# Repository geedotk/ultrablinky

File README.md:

# Ultrablinky Hardware

Ultrablinky is a strobelight/stroboscope that has multiple blink modes and can be triggered by different stimuli. If blinking an LED is the "Hello, world!" of the hardware/firmware world, Ultrablinky is the equivalent of shouting "HELLO, WORLD!"

## Use cases:
- Camera strobe, where a set number of flashes are triggered by motion
- Continuous flashing, because you know you want to pretend like you're at a rave
- Flashing synchronized with sound, because you still want to pretend you're at a rave, but you got tired of the asynchronous flashing
- Continuous flashing to freeze repetitive motion. Although it will look like the motion is stopped, don't be an idiot and stick your fingers in it, because it will hurt.
- Do other cool stuff that hasn't been thought of yet.

## Hardware
The "blinky" in the Ultrablinky is a 100W COB LED. This LED has forward voltage Vf of
30V-36V with a current of 3.5A.

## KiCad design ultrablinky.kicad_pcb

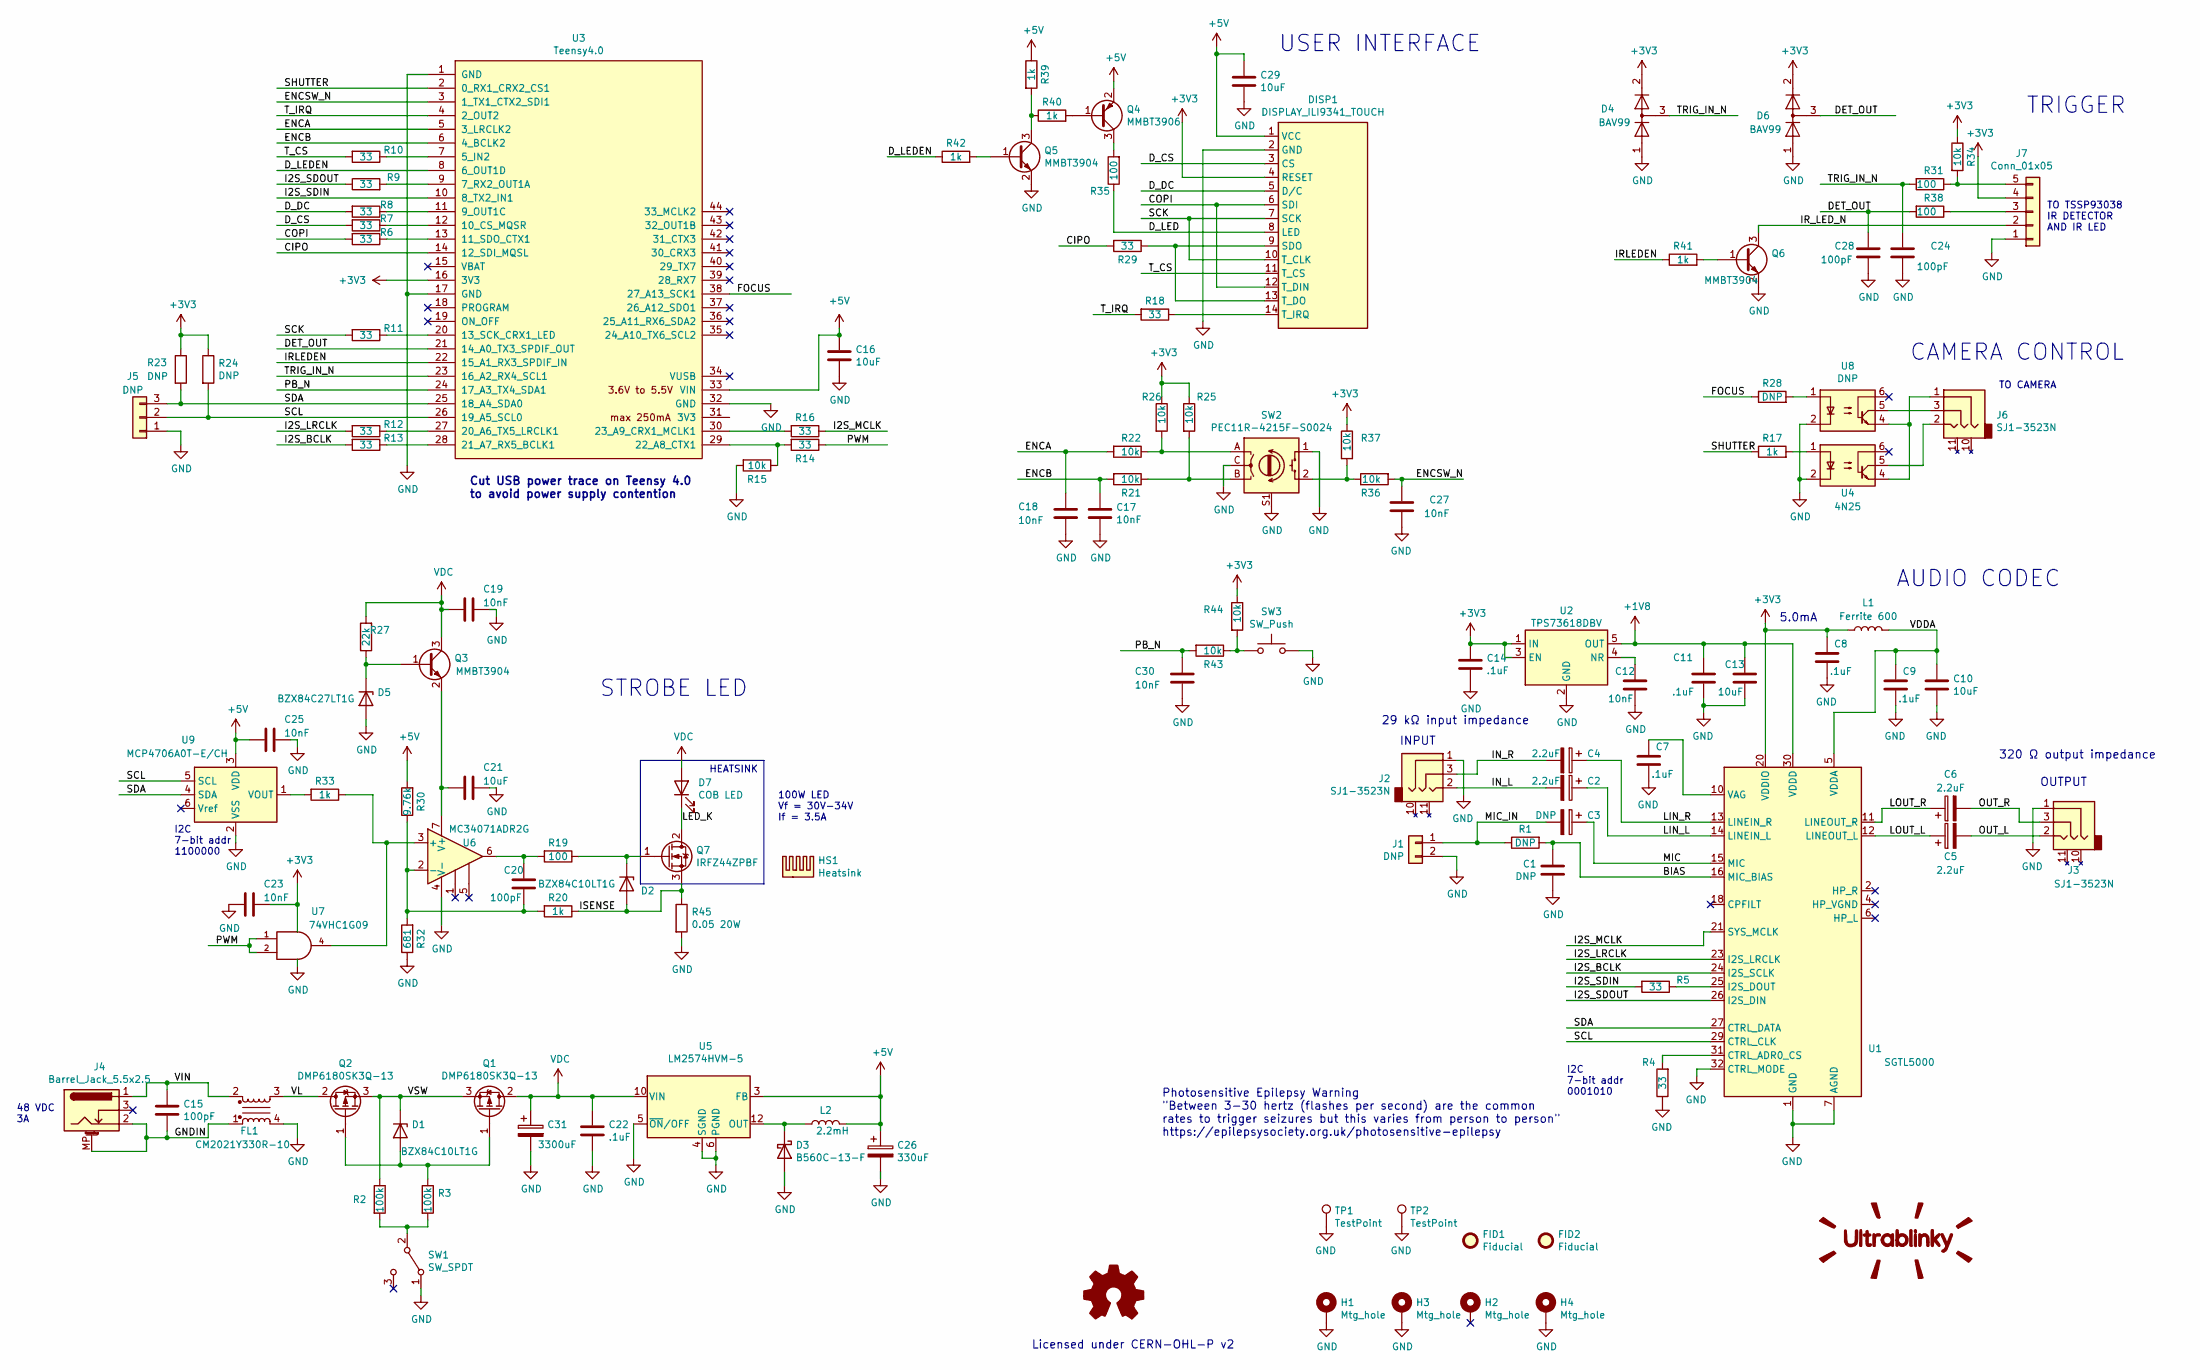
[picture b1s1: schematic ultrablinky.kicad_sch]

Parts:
C1: DNP; C_1206_3216Metric
C2, C4, C5, C6: 2.2uF; CP_Elec_4x5.7
C3: DNP; CP_Elec_4x5.7
C7, C8, C9, C11, C14, C22: .1uF; R_0805_2012Metric
C10, C13, C16, C21, C29: 10uF; C_1206_3216Metric
C12, C17, C18, C19, C23, C25, C27, C30: 10nF; C_0805_2012Metric
C15, C20, C24, C28: 100pF; C_0805_2012Metric
C26: 330uF; CP_Elec_8x10
C31: 3300uF; CP_Radial_L40.0mm_D20.0mm_P7.50mm_Horizontal
D1, D2: BZX84C10LT1G; D_SOT-23_ANK
D3: B560C-13-F; D_SMC
D4, D6: BAV99; SOT-23
D5: BZX84C27LT1G; D_SOT-23_ANK
D7: COB LED; LED_COB_100W
DISP1: DISPLAY_ILI9341_TOUCH
FID1, FID2: Fiducial; Fiducial_1mm_Mask2mm
FL1: CM2021Y330R-10; CM2021Y330R10
H1, H2, H3, H4: Mtg_hole; MountingHole_3.2mm_M3_DIN965_Pad
HS1: Heatsink; Heatsink_70x70mm_ATS-CPX070070025-136-C2-R0
J1: DNP; PinHeader_1x02_P2.54mm_Vertical
J2, J3, J6: SJ1-3523N; SJ13523N1_TRS_Jack
J4: Barrel_Jack_5.5x2.5; CUI_PJ-079BH
J5: DNP; PinHeader_1x03_P2.54mm_Vertical
J7: Conn_01x05; Molex_Mini-Fit_Jr_39-30-3055_1x05_P4.20mm_Horizontal
L1: Ferrite 600; L_0805_2012Metric
L2: 2.2mH; L_12x12mm_H10mm
LOGO1: Ultrablinky_logo; logo_ultrablinky
LOGO2: Logo_Open_Hardware_Small; OSHW-Logo2_9.8x8mm_SilkScreen
Q1, Q2: DMP6180SK3Q-13; TO-252-2
Q3, Q5, Q6: MMBT3904; SOT-23
Q4: MMBT3906; SOT-23
Q7: IRFZ44ZPBF; TO-220-3_Horizontal_TabDown
R1, R23, R24, R28: DNP; R_0805_2012Metric
R2, R3: 100k; R_0805_2012Metric
R4, R5, R6, R7, R8, R9, R10, R11, R12, R13, R14, R16, R18, R29: 33; R_0805_2012Metric
R15, R21, R22, R25, R26, R34, R36, R37, R43, R44: 10k; R_0805_2012Metric
R17, R20, R33, R39, R40, R41, R42: 1k; R_0805_2012Metric
R19, R31, R35, R38: 100; R_0805_2012Metric
R27: 22k; R_0805_2012Metric
R30: 9.76k; R_0805_2012Metric
R32: 681; R_0805_2012Metric
R45: 0.05 20W; TO-220-2_Horizontal_TabDown
SW1: SW_SPDT; SW_EG1213
SW2: PEC11R-4215F-S0024
SW3: SW_Push; SW_PUSH_6mm_H17mm
TP1, TP2: TestPoint; TestPoint_Keystone_5006
U1: SGTL5000; QFN-32-1EP_5x5mm_P0.5mm_EP3.6x3.6mm
U2: TPS73618DBV; SOT-23-5
U3: Teensy4.0; Teensy40
U4: 4N25; 4N25_OPTOCOUPLER_SMD
U5: LM2574HVM-5; SOIC-14W_7.5x9mm_P1.27mm
U6: MC34071ADR2G; SOIC-8_3.9x4.9mm_P1.27mm
U7: 74VHC1G09; SOT-353_SC-70-5_Handsoldering
U8: DNP; 4N25_OPTOCOUPLER_SMD
U9: MCP4706A0T-E/CH; SOT-23-6

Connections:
+1V8: C11.1, C13.1, U1.30 (VDDD), U2.5 (OUT)
+3V3: C8.1, C14.1, C23.1, D4.2 (A), D6.2 (A), DISP1.4 (RESET), J7.4, L1.1, R23.1, R24.1, R25.1, R26.1, R34.1, R37.1, R44.1, U1.20 (VDDIO), U2.1 (IN), U2.3 (EN), U3.16 (3V3), U7.5 (VCC)
+5V: C16.1, C25.2, C26.1, C29.1, DISP1.1 (VCC), L2.2, Q4.2 (E), R30.2, R39.1, U3.33 (VIN), U5.3 (FB), U9.3 (VDD)
/BIAS: C1.1, R1.2, U1.16 (MIC_BIAS)
/CIPO: R29.2, U3.14 (12_SDI_MQSL)
/COPI: DISP1.6 (SDI), DISP1.12 (T_DIN), R6.2
/DET_OUT: C28.1, D6.3 (K), R38.2, U3.21 (14_A0_TX3_SPDIF_OUT)
/D_CS: DISP1.3 (CS), R7.2
/D_DC: DISP1.5 (D/C), R8.2
/D_LED: DISP1.8 (LED), R35.1
/D_LEDEN: R42.1, U3.8 (6_OUT1D)
/ENCA: C18.1, R22.2, U3.5 (3_LRCLK2)
/ENCB: C17.1, R21.2, U3.6 (4_BCLK2)
/ENCSW_N: C27.1, R36.2, U3.3 (1_TX1_CTX2_SDI1)
/FOCUS: R28.1, U3.38 (27_A13_SCK1)
/GNDIN: C15.2, FL1.1, J4.2, J4.MP (MountPin)
/I2S_BCLK: R13.2, U1.24 (I2S_SCLK)
/I2S_LRCLK: R12.2, U1.23 (I2S_LRCLK)
/I2S_MCLK: R16.1, U1.21 (SYS_MCLK)
/I2S_SDIN: R5.2, U3.10 (8_TX2_IN1)
/I2S_SDOUT: R9.1, U1.26 (I2S_DIN)
/IN_L: C2.2, J2.2
/IN_R: C4.2, J2.3
/IRLEDEN: R41.1, U3.22 (15_A1_RX3_SPDIF_IN)
/IR_LED_N: J7.2, Q6.3 (C)
/ISENSE: D2.2 (A), Q7.3 (S), R20.1, R45.1
/LED_K: D7.1 (K), Q7.2 (D)
/LIN_L: C2.1, U1.14 (LINEIN_L)
/LIN_R: C4.1, U1.13 (LINEIN_R)
/LOUT_L: C5.1, U1.12 (LINEOUT_L)
/LOUT_R: C6.1, U1.11 (LINEOUT_R)
/MIC: C3.1, U1.15 (MIC)
/MIC_IN: C3.2, J1.1, R1.1
/OUT_L: C5.2, J3.2
/OUT_R: C6.2, J3.3
/PB_N: C30.1, R43.2, U3.24 (17_A3_TX4_SDA1)
/PWM: R14.1, U7.1, U7.2
/SCK: DISP1.7 (SCK), DISP1.10 (T_CLK), R11.2
/SCL: J5.2, R24.2, U1.29 (CTRL_CLK), U3.26 (19_A5_SCL0), U9.5 (SCL)
/SDA: J5.3, R23.2, U1.27 (CTRL_DATA), U3.25 (18_A4_SDA0), U9.4 (SDA)
/SHUTTER: R17.1, U3.2 (0_RX1_CRX2_CS1)
/TRIG_IN_N: C24.1, D4.3 (K), R31.2, U3.23 (16_A2_RX4_SCL1)
/T_CS: DISP1.11 (T_CS), R10.2
/T_IRQ: R18.2, U3.4 (2_OUT2)
/VDDA: C9.1, C10.1, L1.2, U1.5 (VDDA)
/VIN: C15.1, FL1.2, J4.1
/VL: FL1.3, Q2.2 (D)
/VSW: D1.1 (K), Q1.3 (S), Q2.3 (S), R2.1
GND: C1.2, C7.2, C8.2, C9.2, C10.2, C11.2, C12.2, C13.2, C14.2, C16.2, C17.2, C18.2, C19.1, C21.1, C22.2, C23.2, C24.2, C25.1, C26.2, C27.2, C28.2, C29.2, C30.2, C31.2, D3.2 (A), D4.1 (K), D5.2 (A), D6.1 (K), DISP1.2 (GND), FL1.4, H1.1, H3.1, H4.1, J1.2, J2.1, J3.1, J5.1, J7.1, Q5.2 (E), Q6.2 (E), R4.1, R15.2, R32.1, R45.2, SW1.1 (A), SW2.1, SW2.C, SW2.S1, SW2.S2, SW3.2, TP1.1, TP2.1, U1.1 (GND), U1.3 (GND), U1.7 (AGND), U1.32 (CTRL_MODE), U1.33 (GND), U2.2 (GND), U3.1 (GND), U3.17 (GND), U3.32 (GND), U4.2, U5.1 (NC), U5.2 (NC), U5.4 (SGND), U5.5 (~ON/OFF), U5.6 (PGND), U5.7 (NC), U5.8 (NC), U5.9 (NC), U5.11 (NC), U5.13 (NC), U5.14 (NC), U6.4 (V-), U7.3 (GND), U8.2, U9.2 (VSS)
unnamed: C7.1, U1.10 (VAG)
unnamed: C12.1, U2.4 (NR)
unnamed: C20.1, R19.2, U6.6
unnamed: C20.2, R20.2, R30.1, R32.2, U6.2 (-)
unnamed: C21.2, Q3.2 (E), U6.7 (V+)
unnamed: D1.2 (A), Q1.1 (G), Q2.1 (G), R3.1
unnamed: D2.1 (K), Q7.1 (G), R19.1
unnamed: D3.1 (K), L2.1, U5.12 (OUT)
unnamed: D5.1 (K), Q3.1 (B), R27.1
unnamed: DISP1.9 (SDO), DISP1.13 (T_DO), R29.1
unnamed: DISP1.14 (T_IRQ), R18.1
unnamed: J6.1, U4.4, U8.4
unnamed: J6.2, U4.5
unnamed: J6.3, U8.5
unnamed: J7.3, R38.1
unnamed: J7.5, R31.1, R34.2
unnamed: Q4.1 (B), R40.2
unnamed: Q4.3 (C), R35.2
unnamed: Q5.1 (B), R42.2
unnamed: Q5.3 (C), R39.2, R40.1
unnamed: Q6.1 (B), R41.2
unnamed: R2.2, R3.2, SW1.2 (B)
unnamed: R4.2, U1.31 (CTRL_ADR0_CS)
unnamed: R5.1, U1.25 (I2S_DOUT)
unnamed: R6.1, U3.13 (11_SDO_CTX1)
unnamed: R7.1, U3.12 (10_CS_MQSR)
unnamed: R8.1, U3.11 (9_OUT1C)
unnamed: R9.2, U3.9 (7_RX2_OUT1A)
unnamed: R10.1, U3.7 (5_IN2)
unnamed: R11.1, U3.20 (13_SCK_CRX1_LED)
unnamed: R12.1, U3.27 (20_A6_TX5_LRCLK1)
unnamed: R13.1, U3.28 (21_A7_RX5_BCLK1)
unnamed: R14.2, R15.1, U3.29 (22_A8_CTX1)
unnamed: R16.2, U3.30 (23_A9_CRX1_MCLK1)
unnamed: R17.2, U4.1
unnamed: R21.1, R25.2, SW2.B
unnamed: R22.1, R26.2, SW2.A
unnamed: R28.2, U8.1
unnamed: R33.1, U6.3 (+), U7.4
unnamed: R33.2, U9.1 (VOUT)
unnamed: R36.1, R37.2, SW2.2
unnamed: R43.1, R44.2, SW3.1
VDC: C19.2, C22.1, C31.1, D7.2 (A), Q1.2 (D), Q3.3 (C), R27.2, U5.10 (VIN)

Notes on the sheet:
48 VDC 3A
320 Ω output impedance
5.0mA
AUDIO CODEC
USER INTERFACE
TO CAMERA
OUTPUT
I2C 7-bit addr 0001010
100W LED Vf = 30V-34V If = 3.5A
TO TSSP93038 IR DETECTOR AND IR LED
TRIGGER
I2C 7-bit addr 1100000
Cut USB power trace on Teensy 4.0 to avoid power supply contention
HEATSINK
INPUT
29 kΩ input impedance
Licensed under CERN-OHL-P v2
CAMERA CONTROL
STROBE LED
Photosensitive Epilepsy Warning "Between 3-30 hertz (flashes per second) are the common rates to trigger seizures but this varies from person to person" https://epilepsysociety.org.uk/photosensitive-epilepsy

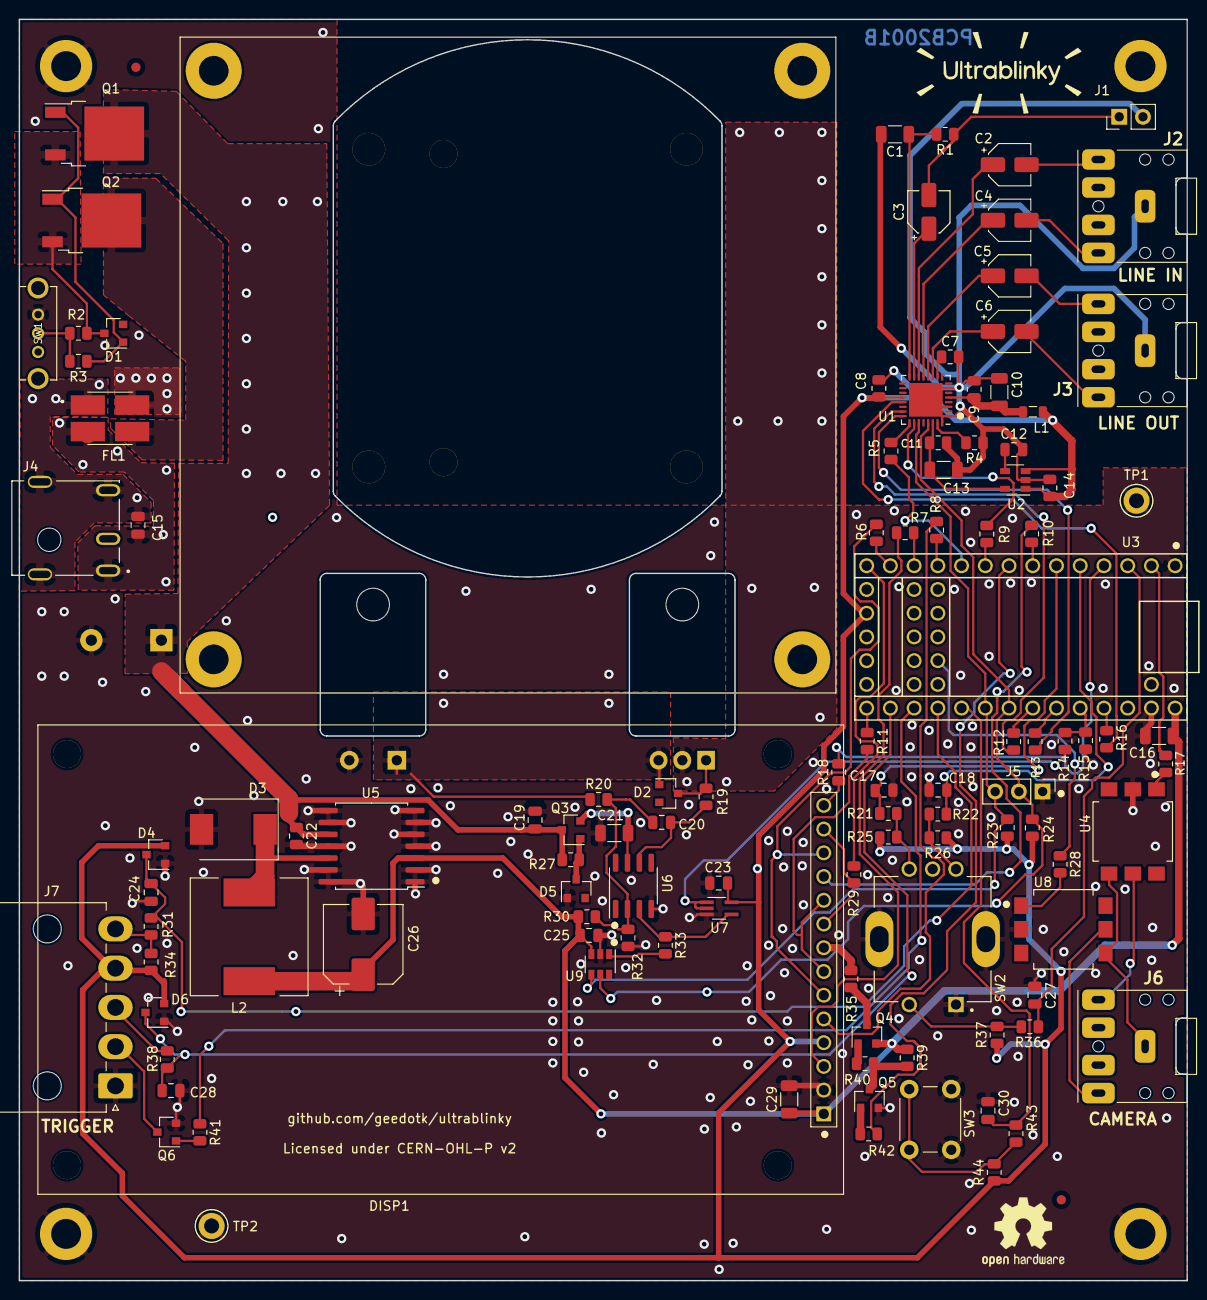
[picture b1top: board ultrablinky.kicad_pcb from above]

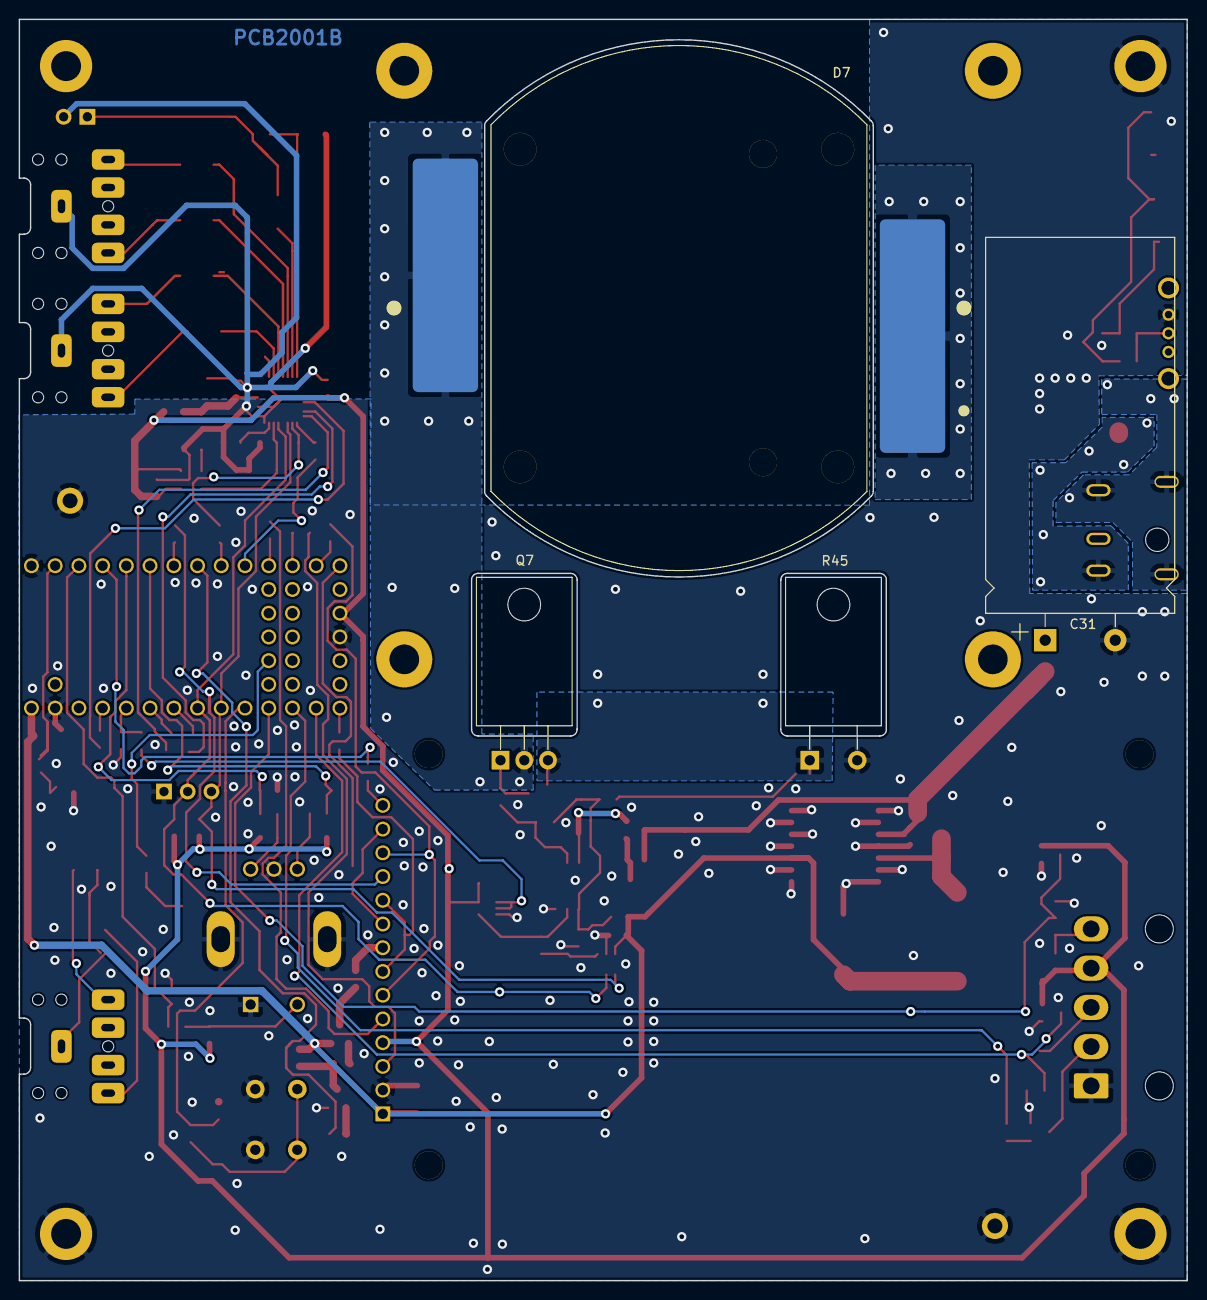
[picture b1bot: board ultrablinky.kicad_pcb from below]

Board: 2 copper layers, 125.0 x 135.0 mm, 124 parts (4 on the bottom side), 92 nets.

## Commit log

2021-04-15 First version of Ultrablinky strobe
    KiCad schematics and PCB (PCB2001A) for Ultrablinky strobe.
2021-04-26 Changed C12 from 50V to 100V
    This was changed so that the same 10nF cap could be used in all
    locations instead of having two different 10nF parts
2021-05-26 Corrected the I2S_SDIN and I2S_SDOUT pins
    Previously, the I2S_SDIN and I2S_SDOUT pins were connected to pins 7 and
    8 of the Teensy package. However, they should have been connected to
    Arduino digital I/O pins 7 and 8 instead. These pins are actually pins
    10 and 9 of the Teensy package. Pins 10 and 9 of the Teensy package were
    instead connected to T_CS and D_LEDEN.
    In order to fix this problem, the signals on pins 7 and 10 (I2S_SDIN and
2021-05-31 Improve rise/fall time
    Changed C21 from 10nF to 100pF
2021-05-31 Fixed LED staying on when it shouldn't be
    Previously there were two times when the strobe LED stayed on when it
    was supposed to be off. First, when the system started, the PWM pin
    would float and would not turn off the LED. Secondly, the non-inverting
    input of the op amp would not go low enough to completely turn off off
    the LED.
    The startup problem was fixed by adding a 10k pull-up resistor to the
2021-06-01 Fixed low drive voltage for LED MOSFET
    The MC34071ADR2G op amp has a Voh that may be as low as 3.7V when
    powered with 5V, which is
    not enough to fully turn on the COB LED MOSFET. The power supply was
    changed to 36V to allow a much higher voltage.
    Also added a 10V zener across the gate and source of the COB LED MOSFET
    to avoid having the voltage exceed the maximum Vgs which is 20V.
2021-06-05 Increased voltage from 36V to 48V
    Previously, the op amp was supplied voltage directly from the 36V power
    supply. However, this was not high enough to drive the COB LED to high
    currents. Now, the voltage has been increased to 48V, but this
    necessitated regulating the voltage to the MC34071A because it cannot
    handle 48V.
2021-06-06 Increase C22 to 22uF
    C22 was changed to 22uF to provide better filter of the op amp power
    supply
2021-06-07 Changed current-sense resistor to allow higher current
    The current-sense resistor R43 was changed from 0.5-ohm to 0.05-ohm to
    allow more current while keeping the voltage across the resistor lower.
    Additionally, a pull-down resistor was added to the op amp non-inverting
    input so that a current-sense voltage of 0V to 12V gets converted to a
    range of 0.2V to 4.9V at the non-inverting input of the op amp.
    Additionally, the voltage divider on the Vref input of the MCP4706A DAC
2021-06-15 Fixed inverted logic of PWM enable
    The NPN transistor has now been replaced with a 74VHC1G09 open-drain
    driver. This means that when the PWM output of the Teensy is low, the
    DAC will also be low instead of being inverted
2021-06-16 Increased bus cap to 3300uF
    The bus capacitance needs to be high enough to allow for short pulses of
    much higher current than the power supply can put out so a large value
    is needed
2021-06-16 Changed film caps to electrolytic
    The film caps in the audio path were changed to electrolytic in order to
    bring down the cost and have better availability
2021-06-18 Added Ultrablinky logo symbol and footprint
2021-06-19 Updated PCB with schematic changes
    The rev B PCB now has the I2S SDIN and I2S SDOUT pins corrected. The
    power supply has been changed to 48V. The PWM logic has been inverted.
    The bus capacitance has been increased to 3300uF. The capacitors in the
    audio path have been changed from film caps to electrolytic. The
    Ultrablinky logo has been added.
2021-06-19 Corrected 4N25 footprints
    Previously the 4N25 footprints were too narrow for the pins.
2021-06-19 Added two additional bypass caps
    The voltage regulator for the op amp and the 74VHC1G09 did not have
    bypass caps previously
2021-06-19 Eliminated 5v-3.3v regulator
    The Teensy 4.0 has a 3.3V pin that can supply up to 250mA, so that is
    now the source for 3.3V.
2021-06-20 General cleanup and generate Gerbers
2021-06-20 Changed 22uF cap to 10uF to reduce BOM cost
2021-06-20 Changed DAC part to change I2C address
    The DAC was changed from MCP4706A1 to MCP4706A0. This is the same
    functionality, but the I2C address was changed from 1100001 to 1100000.
    This part seems to have somewhat better availability.
2022-03-14 Updated KiCad version to 6.0.2
